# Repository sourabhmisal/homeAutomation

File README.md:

# Home Automation

A basic retrofit home automation system

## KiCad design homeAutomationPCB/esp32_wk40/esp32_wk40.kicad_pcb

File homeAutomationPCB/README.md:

# Home Automation PCB

Authors: Manu S, Sourabh Misal

This is basic PCB which controls lights and devices under 16A

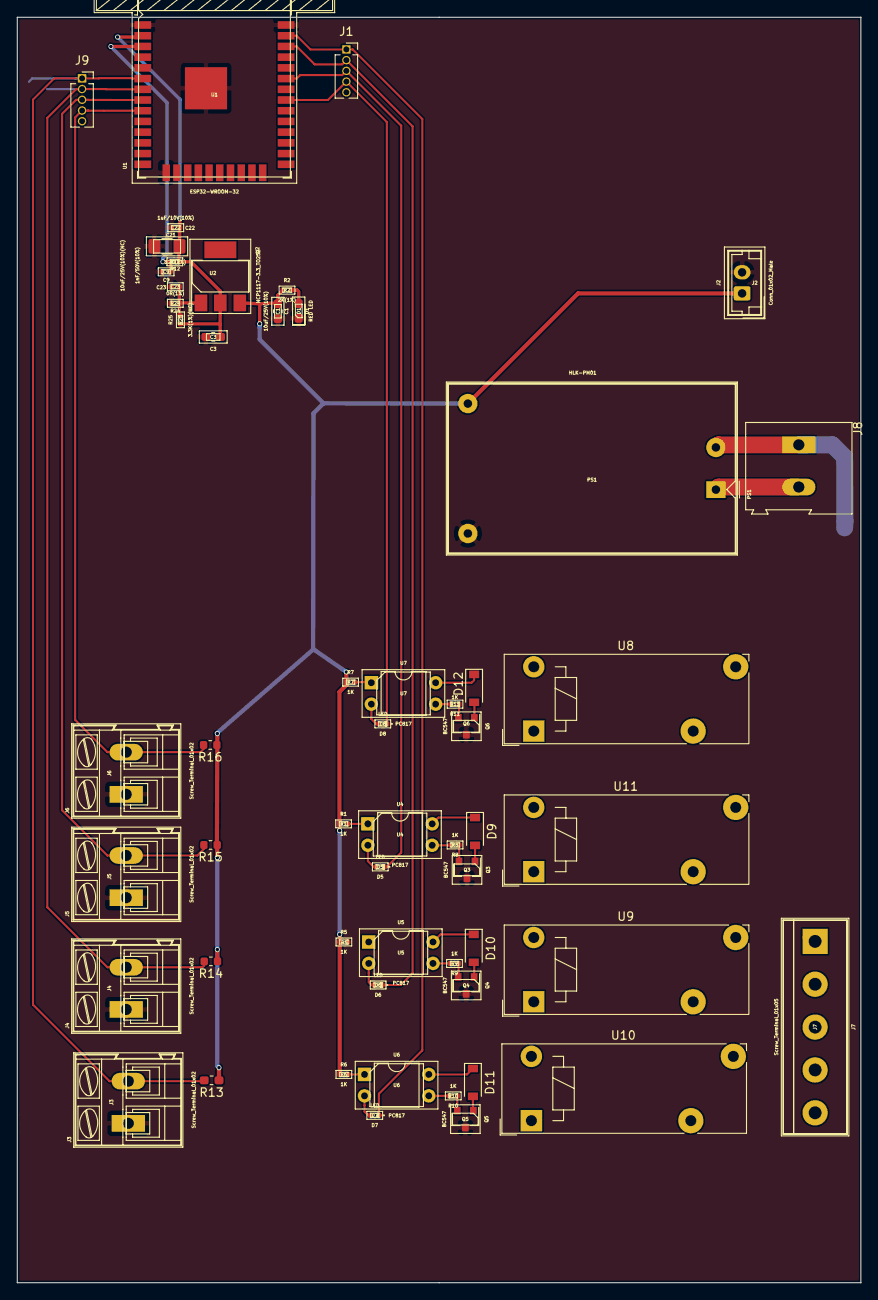
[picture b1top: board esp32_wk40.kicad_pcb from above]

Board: 4 copper layers, 100.0 x 150.0 mm, 55 parts (0 on the bottom side), 44 nets.

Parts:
C1: 10uF/25V(10%); C_0603_1608Metric_Pad1.05x0.95mm_HandSolder
C3: 22uF/25V(10%); C_0603_1608Metric_Pad1.05x0.95mm_HandSolder
C9: 1nF/50V(10%); C_0402_1005Metric
C21: 100uF/6.3V(20%); C_1206_3216Metric_Pad1.42x1.75mm_HandSolder
C22: 1uF/10V(10%); C_0402_1005Metric
C23: 10uF/25V(10%)(NC); C_0402_1005Metric
D1: RED LED; LED_0603_1608Metric_Pad1.05x0.95mm_HandSolder
D5, D6, D7, D8: LED; LED_0402_1005Metric
D9, D10, D11, D12: 1N4007; D_SOD-123
J1, J9: Conn_01x05_Male; PinSocket_1x05_P1.27mm_Vertical
J2: Conn_01x02_Male; JST_EH_B2B-EH-A_1x02_P2.50mm_Vertical
J3, J4, J5, J6, J8: Screw_Terminal_01x02; TerminalBlock_Altech_AK300-2_P5.00mm
J7: Screw_Terminal_01x05; TerminalBlock_bornier-5_P5.08mm
PS1: HLK-PM01; Converter_ACDC_HiLink_HLK-PMxx
Q3, Q4, Q5, Q6: BC547; SOT-23
R1, R5, R6, R7, R8, R9, R10, R11: 1K; R_0402_1005Metric
R2: 2K(1%); R_0402_1005Metric
R12: 12K(1%); R_0402_1005Metric
R13: 10k; R_0603_1608Metric_Pad1.05x0.95mm_HandSolder
R14, R15, R16: 10k; R_0603_1608Metric
R24: 0R(1%); R_0402_1005Metric
R25: 3.3K(1%)(NC); R_0402_1005Metric
U1: ESP32-WROOM-32
U2: NCP1117-3.3_TO252; SOT-223
U4, U5, U6, U7: PC817; DIP-4_W7.62mm
U8, U9, U10, U11: RZ03-1A3-D005; Relay_1-Form-A_Schrack-RYII_RM5mm

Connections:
+3V3: C3.1, C21.1, C22.1, R12.2, R25.1, U1.2, U2.2
+5V: C1.1, J2.1, PS1.4, R1.1, R2.1, R5.1, R6.1, R7.1, R13.1, R14.1, R15.1, R16.1, U2.3
/IO19: D8.1, J1.4, U1.31
/IO21: D5.1, J1.3, U1.33
/IO22: D6.1, J1.2, U1.36
/IO23: D7.1, J1.1, U1.37
/IO32: J5.2, J9.3, R15.2, U1.8
/IO33: J6.2, J9.4, R16.2, U1.9
/IO34: J3.2, J9.1, R13.2, U1.6
/IO35: J4.2, J9.2, R14.2, U1.7
GND: C1.2, C3.2, C9.2, C21.2, C22.2, C23.2, D1.1, J2.2, J3.1, J4.1, J5.1, J6.1, PS1.3, Q3.3, Q4.3, Q5.3, Q6.3, R24.2, U1.1, U1.15, U1.38, U1.39
unnamed: C9.1, R12.1, U1.3
unnamed: C23.1, R24.1, R25.2, U2.1
unnamed: D1.2, R2.2
unnamed: D5.2, U4.2
unnamed: D6.2, U5.2
unnamed: D7.2, U6.2
unnamed: D8.2, U7.2
unnamed: D9.1, U4.4
unnamed: D9.2, Q3.1
unnamed: D10.1, U5.4
unnamed: D10.2, Q4.1
unnamed: D11.1, U6.4
unnamed: D11.2, Q5.1
unnamed: D12.1, U7.4
unnamed: D12.2, Q6.1
unnamed: J7.2, U8.11
unnamed: J7.3, U11.11
unnamed: J7.4, U9.11
unnamed: J7.5, U10.11
unnamed: J8.1, PS1.2
unnamed: J8.2, PS1.1
unnamed: Q3.2, R8.1
unnamed: Q4.2, R9.1
unnamed: Q5.2, R10.1
unnamed: Q6.2, R11.1
unnamed: R1.2, U4.1
unnamed: R5.2, U5.1
unnamed: R6.2, U6.1
unnamed: R7.2, U7.1
unnamed: R8.2, U4.3
unnamed: R9.2, U5.3
unnamed: R10.2, U6.3
unnamed: R11.2, U7.3

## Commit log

2020-10-06 Initial PCB Sketch
2020-10-06 Added CHANGELOG.rst
